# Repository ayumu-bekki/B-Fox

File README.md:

[English documentation is available here](./README.en.md)

# B-Fox

# B-Fox App Store (iOS)

https://apps.apple.com/jp/app/b-fox-receiver/id6759365457

# B-Fox Beacon Control Panel
https://ayumu-bekki.github.io/B-Fox/bfox_beacon/web_client/

## 概要
B-Fox は、Bluetooth Low Energy (BLE) を利用し、Foxハンティングの遊びを再現・実現するためのオープンソースプロジェクトです。
導入・参加の障壁を下げ、「電波の強弱で隠し場所を探す」という無線方向探索のコアな楽しさを手軽に実現することを目指しています。

このプロジェクトを始めるにあたり、既存のFoxハンティング・ARDFに以下のような課題があり手軽でないと感じていました。
- 送信機・受信機のコストが高い
- 運用(ビーコン設置)に免許が必要
- アマチュア無線の帯域を利用するため、商用利用が不可 
- ARDFは競技のため厳格なルールがある

そこで、誰でも免許なしに利用できるBLEを利用して手軽に遊べる無線方向探索の遊びを実現します。

## 運用について
基本遊びだが発展としてARDF競技があるという位置付けを想定し、パークARDFを参考にルールを緩くする方向で運用資料(草案)を作成しました。
[B-Fox 運用・ルール案](./operation/OPERATION.md)

## 送信機・受信機について
[送受信機デバイスドキュメント](./docs/README.md) を参考にしてください。
このプロジェクトには、プログラム一式と、PCB・3Dプリンタで出力できるデータが含まれています。

プロトコルにiBeacon (BLE)を利用しているため、LightBlue (https://punchthrough.com/lightblue/) などをインストールすれば遊ぶことができます。

また、iOS向けに専用受信アプリを用意しています。

### QRコードによるビーコン設定
iOS受信アプリでは、QRコードを読み取ってビーコンターゲット（UUID + MajorID）を設定できます。

**QRコードフォーマット:**
```
BFOX:<UUID>:<MajorID>
```

| 要素 | 説明 | 制約 |
|------|------|------|
| `BFOX` | 固定プレフィックス（大文字小文字不問） | 必須 |
| `UUID` | iBeaconのUUID | 標準的なUUID形式 |
| `MajorID` | iBeaconのMajor ID | 整数 0〜65535 |

**例:**
```
BFOX:C65B2C5D-9E53-46EC-8B8E-54D9E2F21188:100
```

### 比較
 
|                    | ARDF                                          | B-Fox                |
| ------------------ | --------------------------------------------- | -------------------- |
| 受信機             | 専用もしくはAM受信機が必要                    | スマートフォンでも可 |
| 資格               | 受信機設置に第3級アマチュア無線技士以上が必要 | 不要                 |
| 無線局免許         | 必要                                          | 不要                 |
| 探知方法           | 音・Sメーター                                 | dBm値                |
| 競技性             | 競技として確立し世界大会がある                | 遊び                 |
| 受信アンテナの自作 | 可能                                          | 基本的に不可         |
| 利用する周波数     | 3.5MHz / 144MHz                               | 2.4GHz               |
| 空中線出力         | 3.5MHz(3-5W) / 144MHz(0.25-1.5W)程度          | 0.06-8mW             |
| 活動範囲           | 数キロメートル                                | 数百メートル         |

## リポジトリ内容説明
送信機・受信機のプログラムと機械設計・運用方法が含まれています。

- bfox_receiver
  - 受信機プログラム一式
- bfox_beacon
  - 送信機プログラム一式
- BFoxReceiverForIOS
  - iOS向け受信用アプリ
- docs
  - 技術資料・PCB・ケース(3Dプリンタ用)
- operation
  - 運用キット

## ライセンス

このプロジェクトは **CERN-OHL-P v2** (CERN Open Hardware Licence Version 2 - Permissive) の下で公開されています。詳細については、[LICENSE](./LICENSE) ファイルを参照してください。

Copyright (c) 2025 Ayumu Bekki

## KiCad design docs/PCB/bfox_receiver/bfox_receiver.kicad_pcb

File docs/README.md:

# B-Foxプロジェクト 技術情報概要

B-Foxは、Bluetooth Low Energy (BLE) を利用し、FOXハンティングの遊びを再現・実現するためのオープンソースプロジェクトです。

---

## 主要コンポーネントとハードウェア

### 送受信機メインモジュール

Seeed Studio XIAO ESP32C6

- BLE による低消費電力での無線通信を実現。
- 外部アンテナ利用可能 技適 (技術基準適合証明) 取得済み
- リポバッテリー対応  携帯利用に適した電源
- 小型フットプリント デバイスの小型化・軽量化

### 受信機インターフェース
キャラクタ液晶表示器を採用
LCDモジュール 16×2行 AQM1602Y-RN-GBW 秋月電子通商取扱([https://akizukidenshi.com/catalog/g/g111916/](https://akizukidenshi.com/catalog/g/g111916/))

---

## ソフトウェアと通信プロトコル

### 開発環境
esp-idf 5.5.1
Espressif IoT Development Framework ([https://github.com/espressif/esp-idf](https://github.com/espressif/esp-idf))

### 通信プロトコル
iBeacon (BLE) プロトコルを利用

GAPを利用し、ビーコン情報を定期的にブロードキャスト
GATTを利用し、送信機の設定変更やバッテリー電圧の取得
スマートフォンアプリ LightBlue ([https://punchthrough.com/lightblue/]https://punchthrough.com/lightblue/)  などで受信可能（この場合、iBeaconではなくGAPによるデバイス名を利用）

---

## ハードウェア製造

送受信機ともにケース・基板 (PCB) のデータを用意しています。
PCBについては、ユニバーサル基板(36x47x1mm)でも作ることが可能です。KiCADの回路図を参考にしてください。
 
PCBWay ([https://www.pcbway.com](https://www.pcbway.com)) などのサービスを利用して基板・ケースの出力が可能です。

- PCB
  - 基板設計情報が含まれています。KiCADで編集が可能です。
    - *_Gerber.zip をそのまま利用できます。(厚さ1mm)
- Case
  - 3Dプリンタで出力できるケースが含まれています。FreeCADで編集が可能です。
    - *.step をそのまま利用できます。

---

##  必要な主要パーツ一覧

リファレンス実装に必要な主要パーツ一覧

### 送信機

| 項目                      | 備考 | 個数 |
| ------------------------- | ---- | ---- |
| Seeed Studio XIAO ESP32C6 |      | 1    |
| リポバッテリー 3000mAh    |      | 1    |

### 受信機

| 項目                          | 備考                                         | 個数 |
| ----------------------------- | -------------------------------------------- | ---- |
| Seeed Studio XIAO ESP32C6     |                                              | 1    |
| 受信機基板                    |                                              | 1    |
| 受信機ケース基盤              |                                              | 1    |
| LCDモジュール AQM1602Y-RN-GBW |                                              | 1    |
| XIAO用ロッドアンテナ          | https://akizukidenshi.com/catalog/g/g117582/ | 1    |
| リポバッテリー 500mAh         |                                              | 1    |
| 抵抗                          | 220kΩ                                        | 2    |
|                               | 1kΩ                                          | 2    |
| XH端子                        | 2P縦型                                       | 2    |
| XH端子付きケーブル            | 2P (ESP32C6のバッテリー接続用)               | 1    |
|                               | 2P横型                                       | 1    |
| コンデンサ                    |                                              |      |
| スライドスイッチ              | 基板実装用                                   | 1    |
| タクトスイッチ                | 基板実装用                                   | 1    |
| ポリスイッチ                  | 250mA                                        | 1    |
| 分割ロングピンソケット        | 9pin                                         | 1    |
|                               | 7pin(ロープロファイル)                       | 2    |
| ネジ                          |                                              |      |
| スペーサー                    |                                              |      |
| 配線用コード                  |                                              | 適量 |

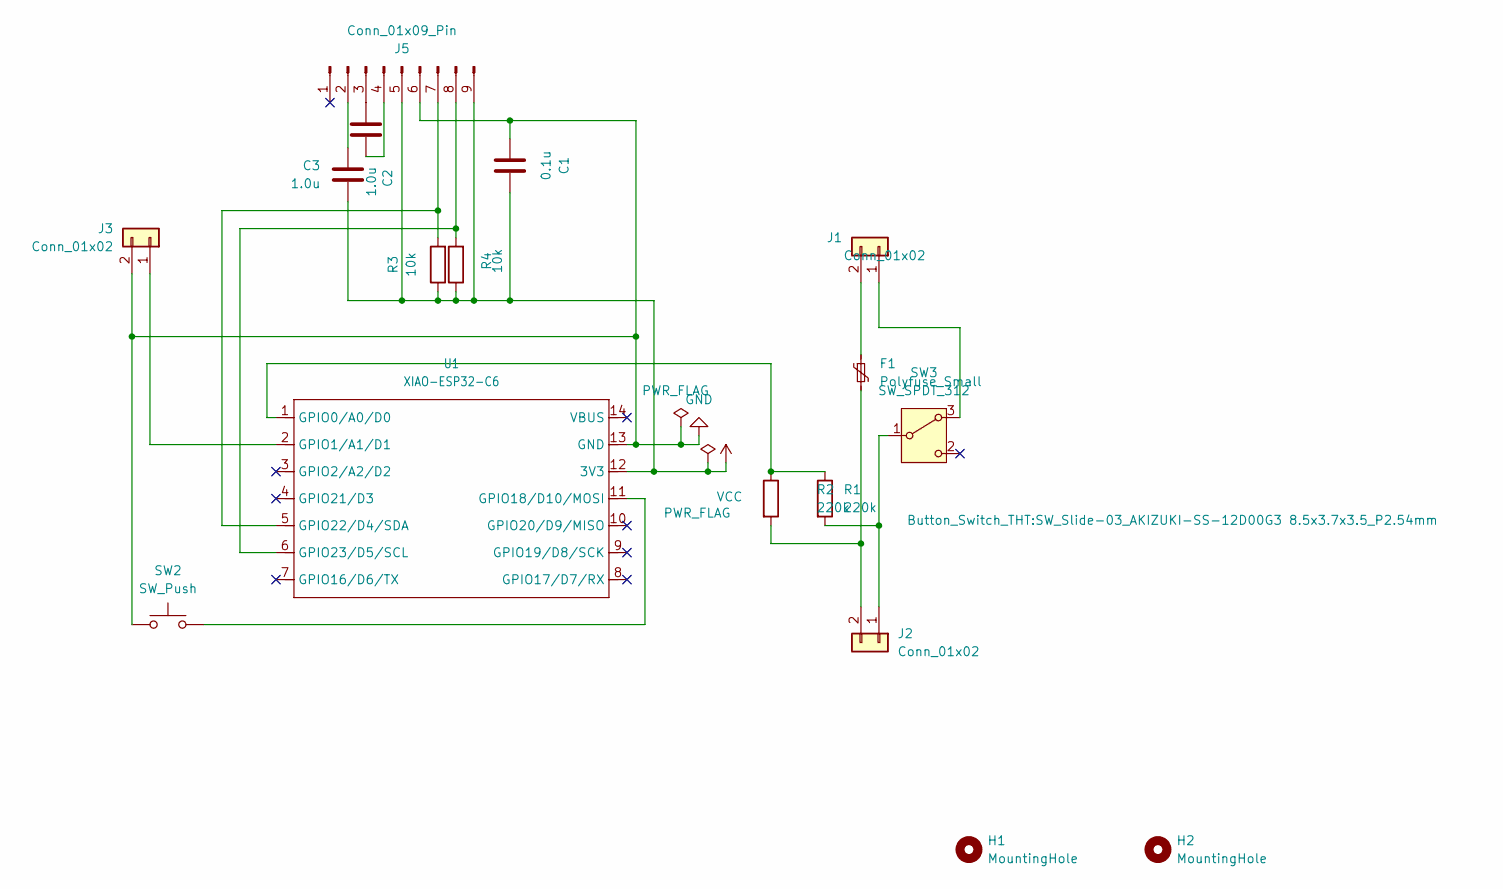
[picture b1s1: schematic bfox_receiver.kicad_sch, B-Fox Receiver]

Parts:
C1: 0.1u; C_Disc_D3.0mm_W1.6mm_P2.50mm
C2, C3: 1.0u; C_Disc_D3.0mm_W1.6mm_P2.50mm
F1: Polyfuse_Small; C_Disc_D4.3mm_W1.9mm_P5.00mm
H1, H2: MountingHole; MountingHole_3.2mm_M3
J1: Conn_01x02; JST_XH_S2B-XH-A-1_1x02_P2.50mm_Horizontal
J2, J3: Conn_01x02; JST_XH_B2B-XH-A_1x02_P2.50mm_Vertical
J5: Conn_01x09_Pin; PinSocket_1x09_P2.54mm_Vertical
R1, R2: 220k; R_Axial_DIN0204_L3.6mm_D1.6mm_P7.62mm_Horizontal
R3, R4: 10k; R_Axial_DIN0204_L3.6mm_D1.6mm_P7.62mm_Horizontal
SW2: SW_Push; SW_PUSH_6mm_H5mm
SW3: SW_SPDT_312; SW_Slide-03_AKIZUKI-SS-12D00G3 8.5x3.7x3.5_P2.54mm
U1: XIAO-ESP32-C6; XIAO-ESP32C6-DIP

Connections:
GND: C1.2, J3.2, J5.6, SW2.1, U1.13 (GND)
unnamed: J1.1, SW3.3 (A)
unnamed: F1.1, J1.2
unnamed: J2.1, R1.2, SW3.1 (B)
unnamed: F1.2, J2.2, R2.2
unnamed: J3.1, U1.2 (GPIO1/A1/D1)
unnamed: C3.2, J5.2
unnamed: C2.1, J5.3
unnamed: C2.2, J5.4
unnamed: J5.7, R3.2, U1.5 (GPIO22/D4/SDA)
unnamed: J5.8, R4.2, U1.6 (GPIO23/D5/SCL)
unnamed: R1.1, R2.1, U1.1 (GPIO0/A0/D0)
unnamed: SW2.2, U1.11 (GPIO18/D10/MOSI)
VCC: C1.1, C3.1, J5.5, J5.9, R3.1, R4.1, U1.12 (3V3)

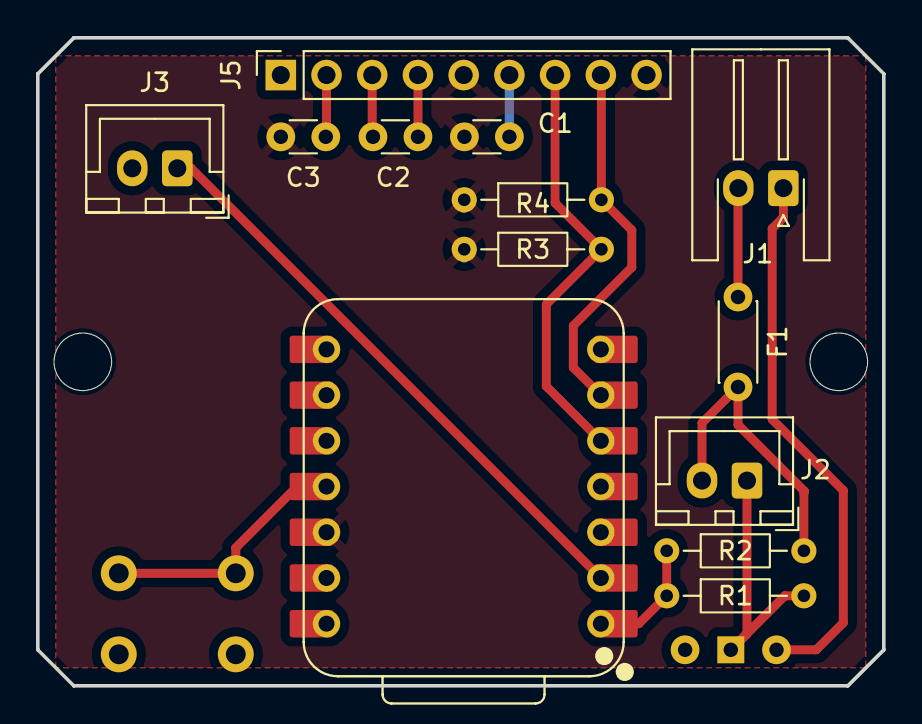
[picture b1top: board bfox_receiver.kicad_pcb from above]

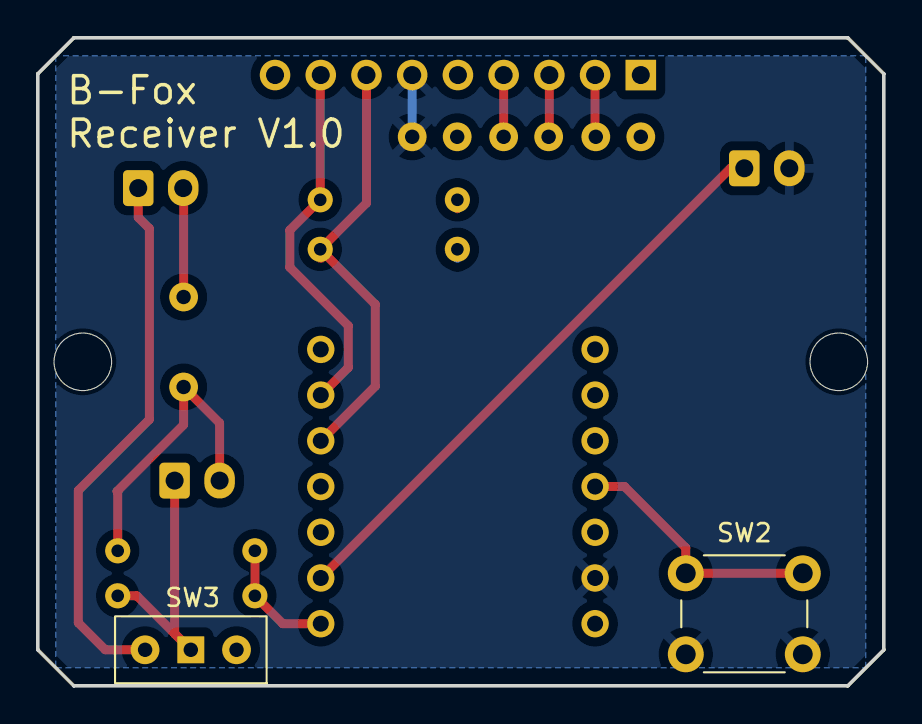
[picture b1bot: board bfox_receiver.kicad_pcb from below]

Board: 2 copper layers, 47.0 x 36.0 mm, 17 parts (2 on the bottom side), 14 nets.

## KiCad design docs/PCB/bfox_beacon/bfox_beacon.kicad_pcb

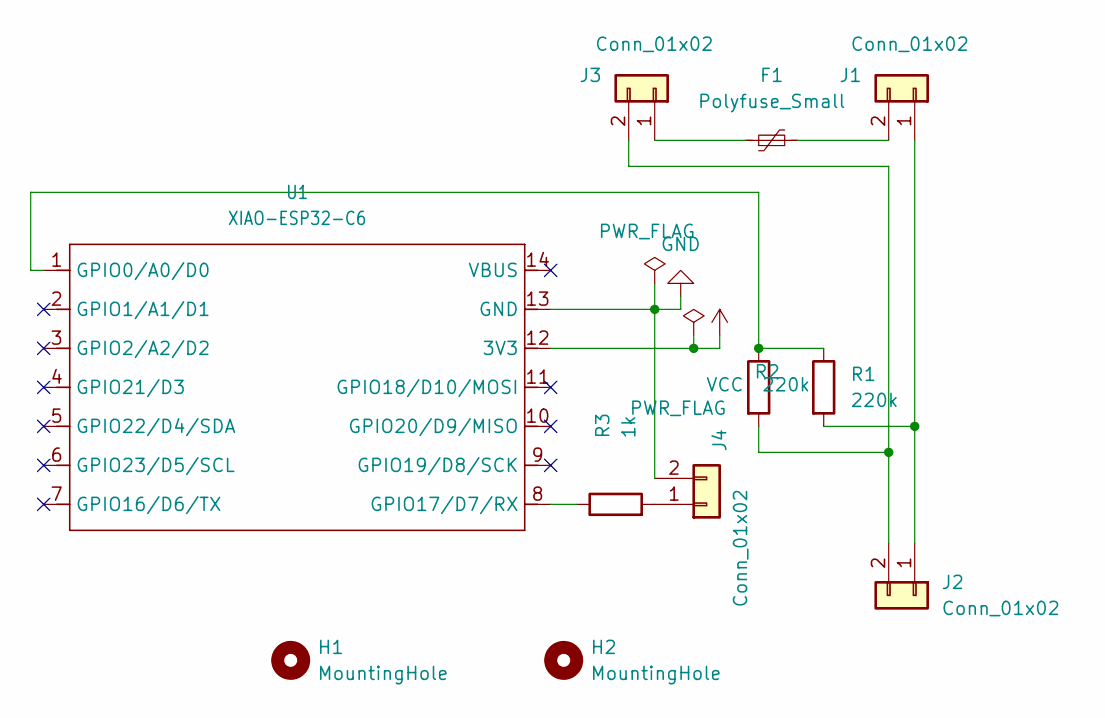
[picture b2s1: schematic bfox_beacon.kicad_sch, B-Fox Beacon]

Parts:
F1: Polyfuse_Small; C_Disc_D4.3mm_W1.9mm_P5.00mm
H1, H2: MountingHole; MountingHole_3.2mm_M3
J1: Conn_01x02; JST_XH_S2B-XH-A-1_1x02_P2.50mm_Horizontal
J2, J3, J4: Conn_01x02; JST_XH_B2B-XH-A_1x02_P2.50mm_Vertical
R1, R2: 220k; R_Axial_DIN0204_L3.6mm_D1.6mm_P7.62mm_Horizontal
R3: 1k; R_Axial_DIN0207_L6.3mm_D2.5mm_P7.62mm_Horizontal
U1: XIAO-ESP32-C6; XIAO-ESP32C6-DIP

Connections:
GND: J4.2, U1.13 (GND)
unnamed: J1.1, J2.1, R1.2
unnamed: F1.2, J1.2
unnamed: J2.2, J3.2, R2.2
unnamed: F1.1, J3.1
unnamed: J4.1, R3.2
unnamed: R1.1, R2.1, U1.1 (GPIO0/A0/D0)
unnamed: R3.1, U1.8 (GPIO17/D7/RX)
VCC: U1.12 (3V3)

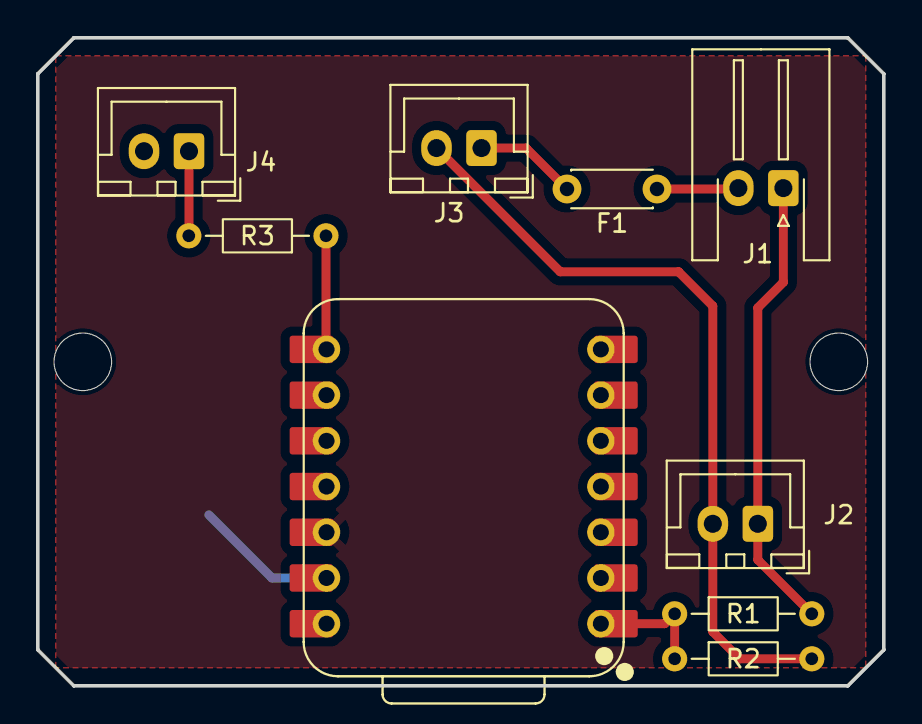
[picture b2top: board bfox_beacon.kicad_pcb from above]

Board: 2 copper layers, 47.0 x 36.0 mm, 11 parts (0 on the bottom side), 8 nets.

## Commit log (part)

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2025-09-30 Update Docments
2025-09-30 Fix Operation docs
2025-09-30 Added beacon and receiver code
2025-09-30 Add English docs, restore Japanese originals
2025-10-01 Update document
2025-10-04 Add PCB data
2025-10-10 Remove Kconfig files and hardcode GPIO configuration
2025-10-10 Foraget add file. Remove Kconfig files and hardcode GPIO configuration
2025-10-10 Update PCB wiring and add 3D case models
2025-10-10 Update monitoring LED pin from D9 to D7 in beacon Update major change button GPIO from D7 to D10 in receiver Change pull resistor mode from pull-up to pull-down for lower power consumption Update .gi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
2025-10-11 Update 3D cases and pcb,hardware documentation
2025-10-11 Fix Receiver PCB Cover
2025-10-20 Add BleRDF Logo for README
2025-10-20 Fix interference of screw holes for cover mounting
2025-10-22 Fix LED Connector Directon BleRDF_Beacon PCB
2025-10-22 Update PCB Gerber data
2025-10-31 Fix PCBCover hole
2025-11-08 change project name. BleRDF -> B-Fox
2025-11-08 Change Logo
2025-11-13 Convert Case StepFile
2025-12-09 fix default bluetooth decice name
2025-12-09 fix webclient project name
2025-12-09 Add Control Panel URL
2025-12-28 Add Deep Sleep Commandt
2025-12-29 Add Deep Sleep mode
2026-02-19 Add BFoxReceiverForIOS Project
2026-02-19 Fix Receiver Case CAD Data and add icon.svg
2026-02-19 fix readme add ios app
2026-02-19 fix readme
2026-02-19 Add Privacy Policy
2026-02-20 Add Reader QR Code
2026-02-21 Remove unnecessary Coded PHY preference setting
2026-02-21 add configurable adv interval via web UI, migrate persistence to NVS
2026-02-21 extend sleep timer on activity
2026-02-21 Fix use continuous BLE scan to reduce NO SIGNAL occurrences
2026-02-21 add battery level bar graph and percentage display to web client
2026-02-21 Fix battery display: show voltage only, ensure bar renders
2026-02-22 Switch to NimBLE stack for iBeacon and GATT services
2026-02-22 Minor fixes
2026-02-22 Fix advertising interval application and change default to 500ms
2026-02-22 bfox receiver Migrate BLE stack to NimBLE and increase beacon expiry and sleep timeouts
2026-02-25 Fix Info.plist localization for App Store Review and add simulator mock data
2026-03-10 Add fine-grained TX power levels from +9dBm to -15dBm for beacon output control
2026-03-10 Update iOS app Build Version
2026-05-05 Add AppStore Link
2026-05-10 iOSアプリに音声案内機能を追加
2026-05-11 アクセシビリティ機能として触感フィードバック機能を追加
2026-05-20 Change license from MIT to Apache License 2.0
2026-05-20 Add beacon configuration QR code documentation
2026-05-20 Change license from Apache-2.0 to BSD-2-Clause-Patent
2026-05-22 relicense project under CERN-OHL-P v2
